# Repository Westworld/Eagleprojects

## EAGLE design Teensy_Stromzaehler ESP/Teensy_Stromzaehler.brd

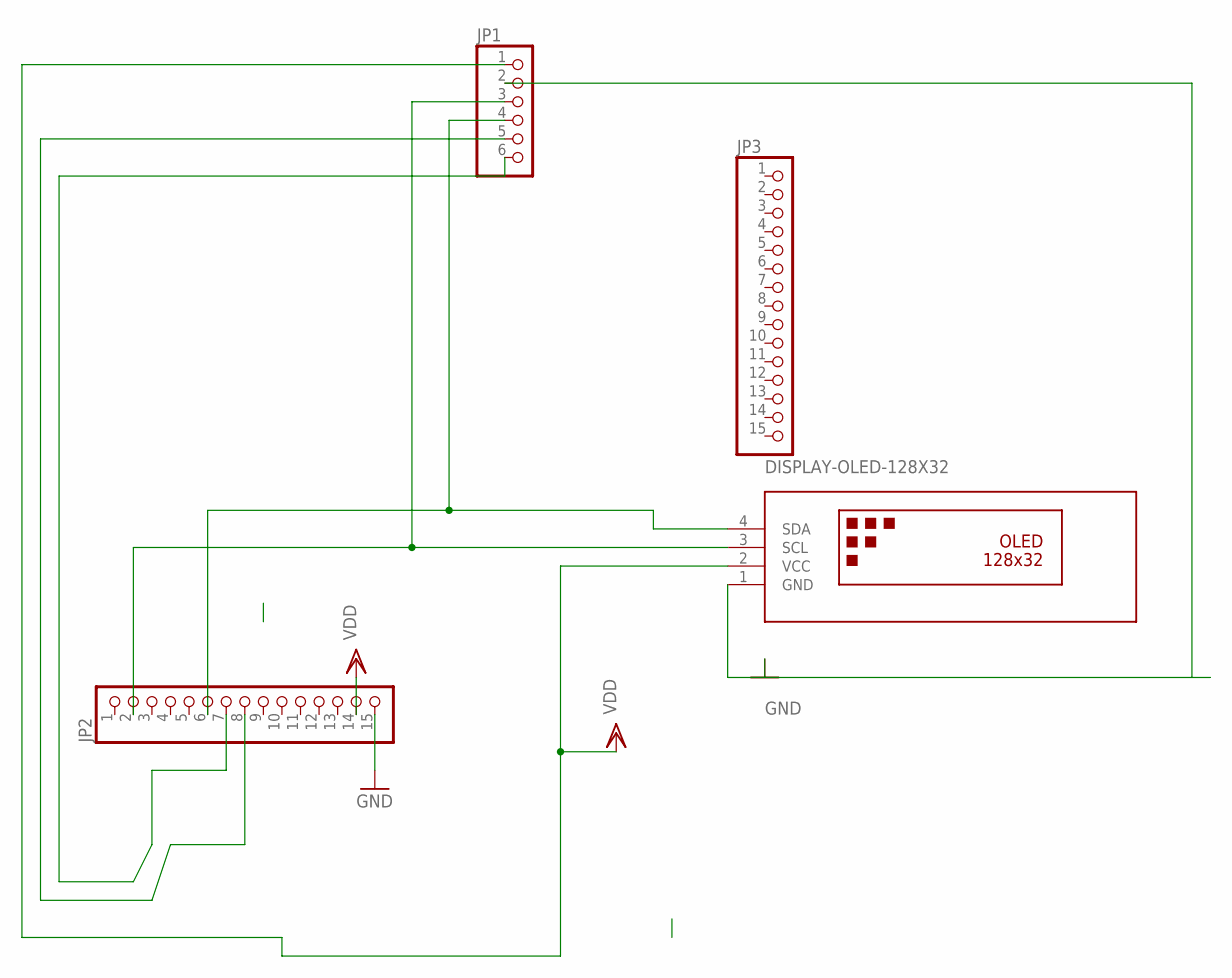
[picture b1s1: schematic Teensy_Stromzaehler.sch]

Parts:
JP1: PINHD-1X6; 1X06
JP2, JP3: PINHD-1X15; 1X15
U$3: DISPLAY-OLED-128X32

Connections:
GND: JP1.2, JP2.15, U$3.1 (GND)
unnamed: JP1.5, JP2.8
unnamed: JP1.6, JP2.7
unnamed: JP1.3, JP2.2, U$3.3 (SCL)
unnamed: JP1.4, JP2.6, U$3.4 (SDA)
VDD: JP1.1, JP2.14, U$3.2 (VCC)

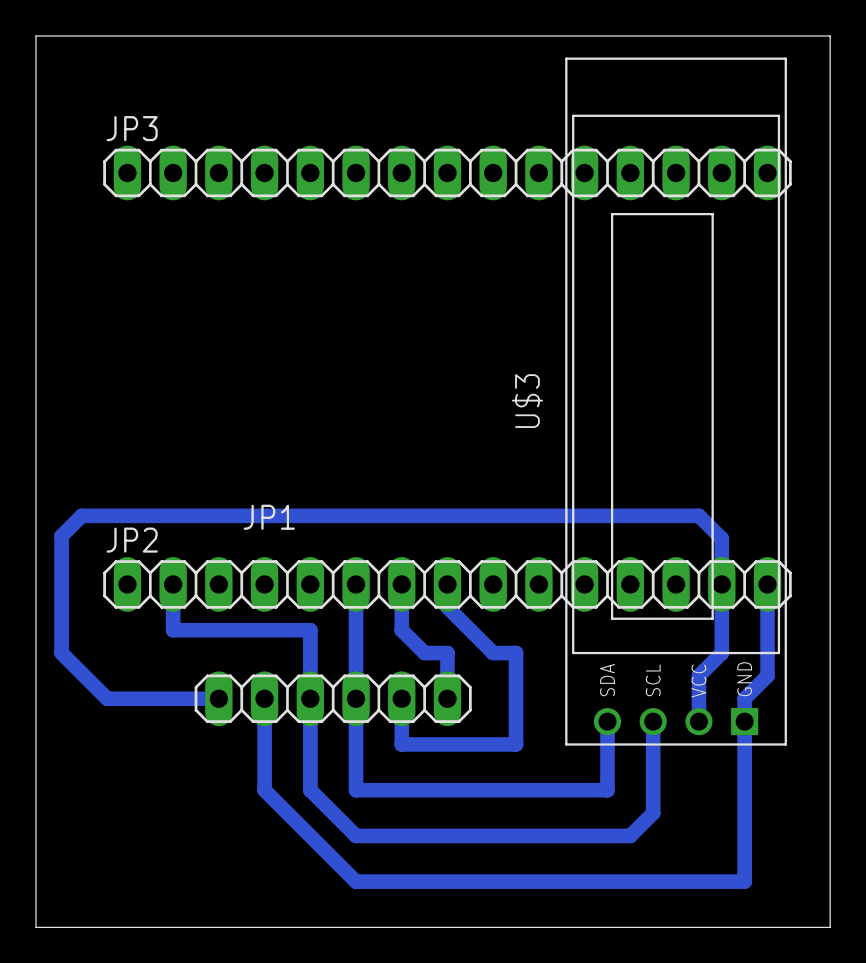
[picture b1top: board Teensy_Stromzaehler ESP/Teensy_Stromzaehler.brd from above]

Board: 2 copper layers, 44.1 x 49.5 mm, 4 parts (0 on the bottom side), 6 nets.

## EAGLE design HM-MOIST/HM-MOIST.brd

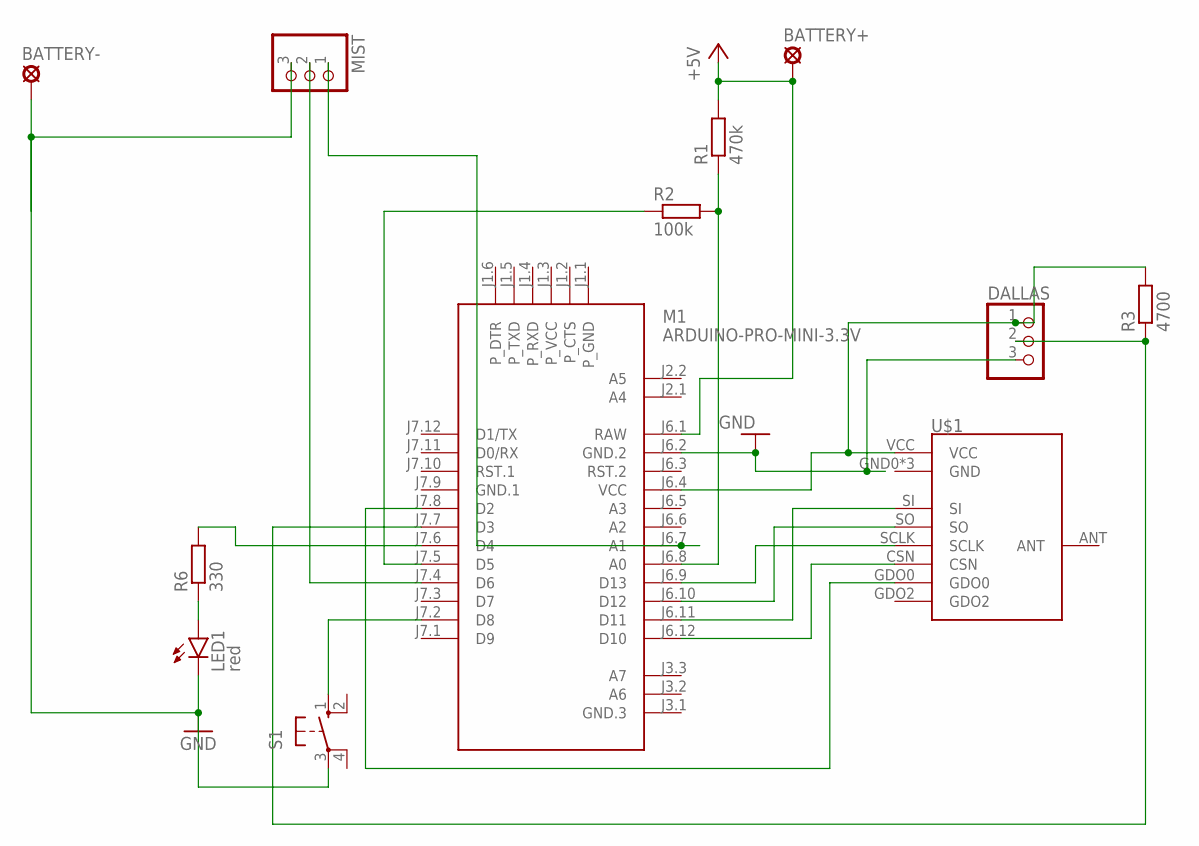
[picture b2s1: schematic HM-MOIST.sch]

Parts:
BATTERY+: LSP11
BATTERY-: LSP11
DALLAS: PINHD-1X3; 1X03
LED1: red; LED5MM
M1: ARDUINO-PRO-MINI-3.3V; ARDUINO-PRO-MINI
MIST: PINHD-1X3; 1X03
R1: 470k; M1206
R2: 100k; 0204/7
R3: 4700; 0204/7
R6: 330; M1206
S1: 10-XX; B3F-10XX
U$1: CC1101

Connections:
+5V: BATTERY+.MP, M1.J6.1 (RAW), R1.2
GND: BATTERY-.MP, DALLAS.3, LED1.K (C), M1.J6.2 (GND.2), MIST.3, S1.3, U$1.GND0 (GND), U$1.GND1 (GND), U$1.GND2 (GND)
GND.1: M1.J7.9 (GND.1)
unnamed: M1.J6.12 (D10), U$1.CSN
unnamed: M1.J7.8 (D2), U$1.GDO0
unnamed: M1.J6.11 (D11), U$1.SI
unnamed: M1.J6.10 (D12), U$1.SO
unnamed: M1.J6.9 (D13), U$1.SCLK
unnamed: LED1.A, R6.1
unnamed: M1.J7.2 (D8), S1.1 (S)
unnamed: M1.J7.6 (D4), R6.2
unnamed: M1.J6.8 (A0), R1.1, R2.2
unnamed: DALLAS.1, M1.J6.4 (VCC), R3.2, U$1.VCC
unnamed: M1.J7.5 (D5), R2.1
unnamed: M1.J7.4 (D6), MIST.2
unnamed: DALLAS.2, M1.J7.7 (D3), R3.1
unnamed: M1.J6.7 (A1), MIST.1

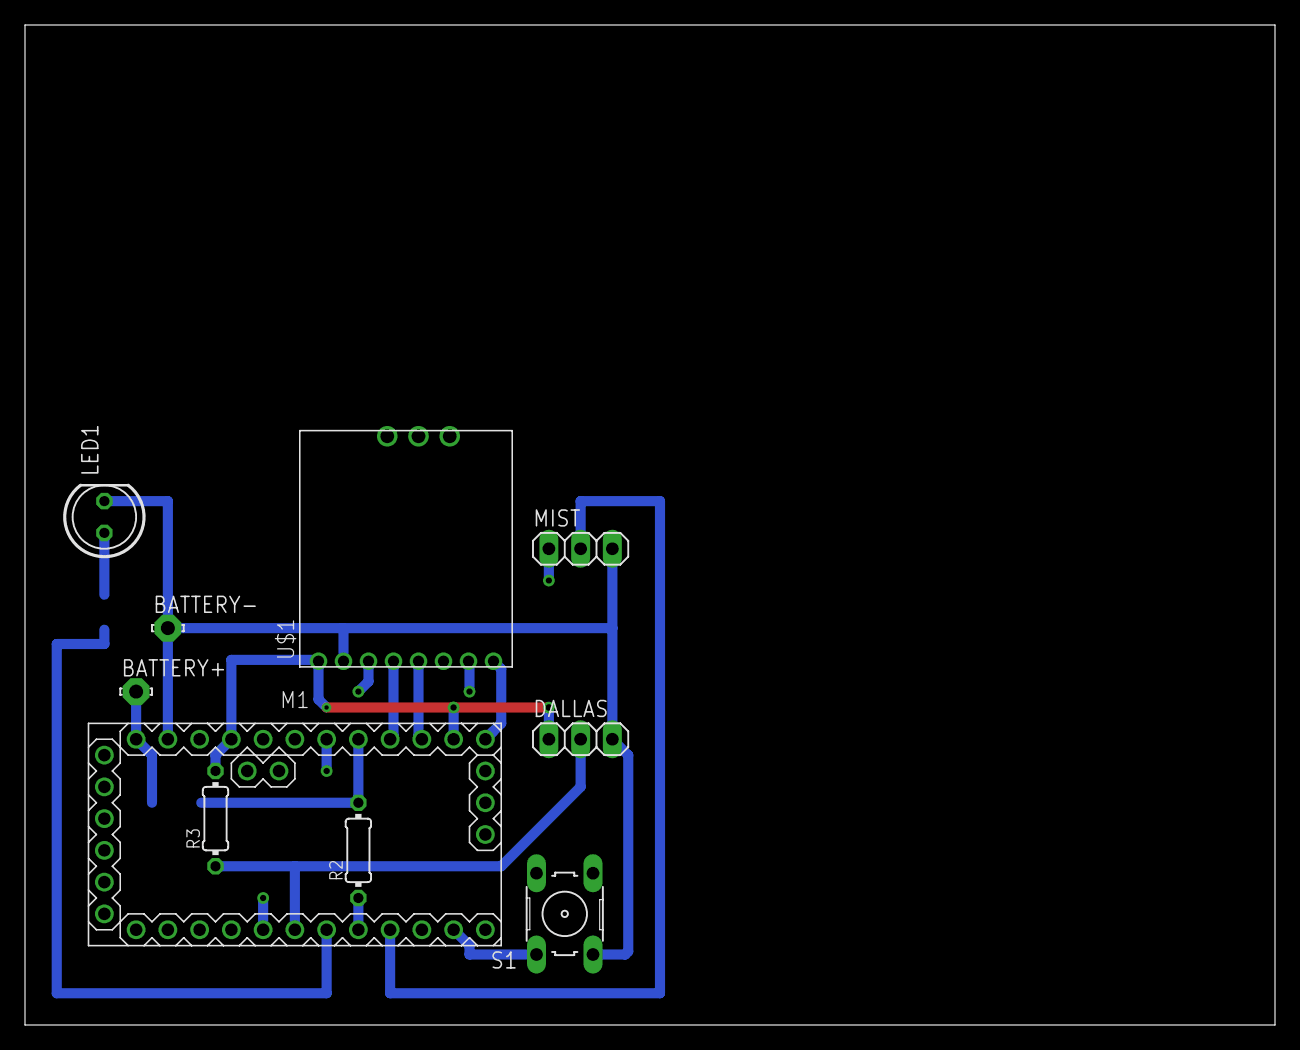
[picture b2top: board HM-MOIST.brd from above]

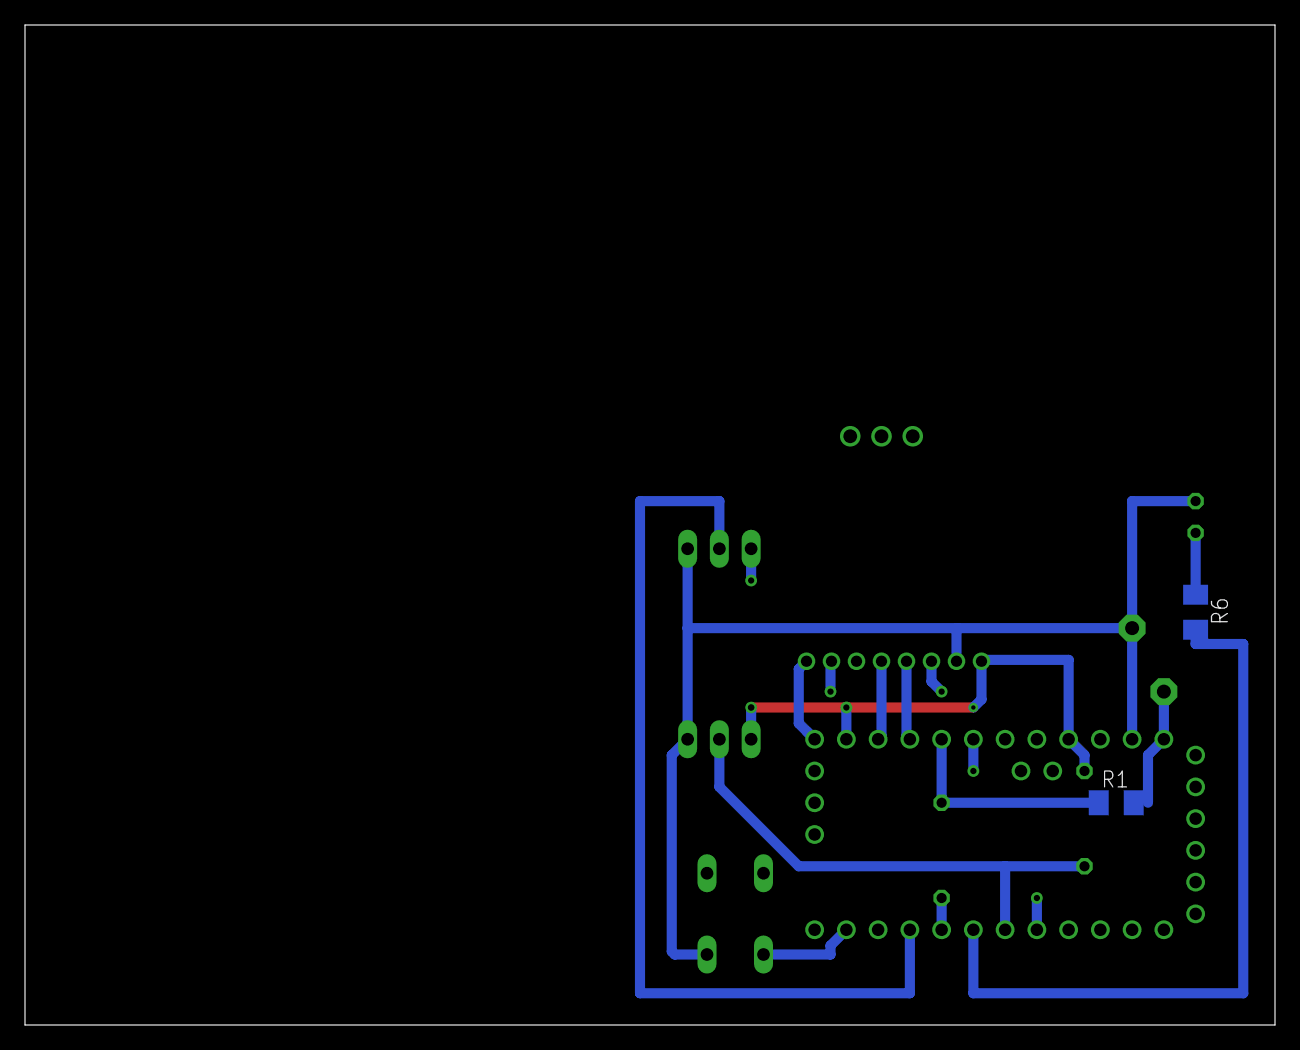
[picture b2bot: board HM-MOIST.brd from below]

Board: 2 copper layers, 100.0 x 80.0 mm, 12 parts (2 on the bottom side), 16 nets.

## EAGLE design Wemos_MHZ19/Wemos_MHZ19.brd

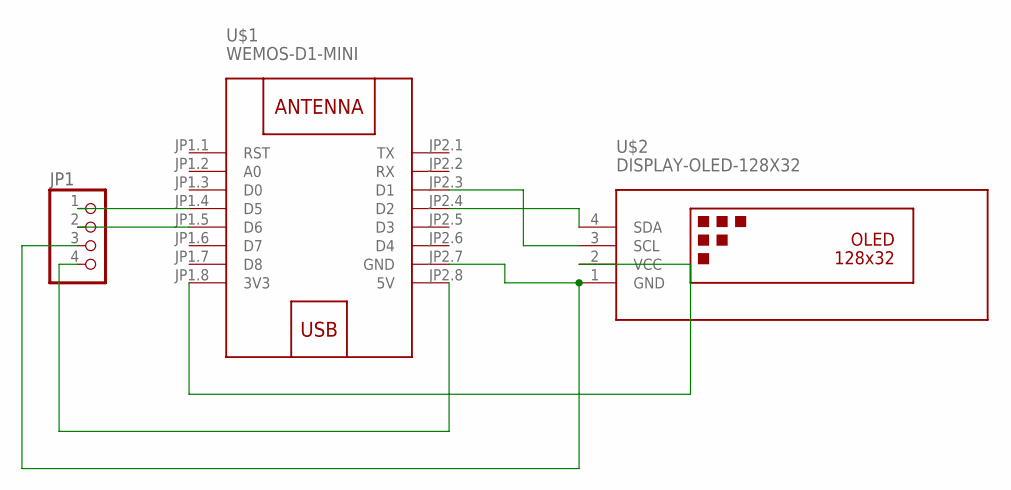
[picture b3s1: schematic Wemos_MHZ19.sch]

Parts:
JP1: PINHD-1X4/90; 1X04/90
U$1: WEMOS-D1-MINI
U$2: DISPLAY-OLED-128X32

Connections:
unnamed: JP1.3, U$1.JP2.7 (GND), U$2.1 (GND)
unnamed: U$1.JP1.8 (3V3), U$2.2 (VCC)
unnamed: U$1.JP2.4 (D2), U$2.4 (SDA)
unnamed: U$1.JP2.3 (D1), U$2.3 (SCL)
unnamed: JP1.4, U$1.JP2.8 (5V)
unnamed: JP1.2, U$1.JP1.5 (D6)
unnamed: JP1.1, U$1.JP1.4 (D5)

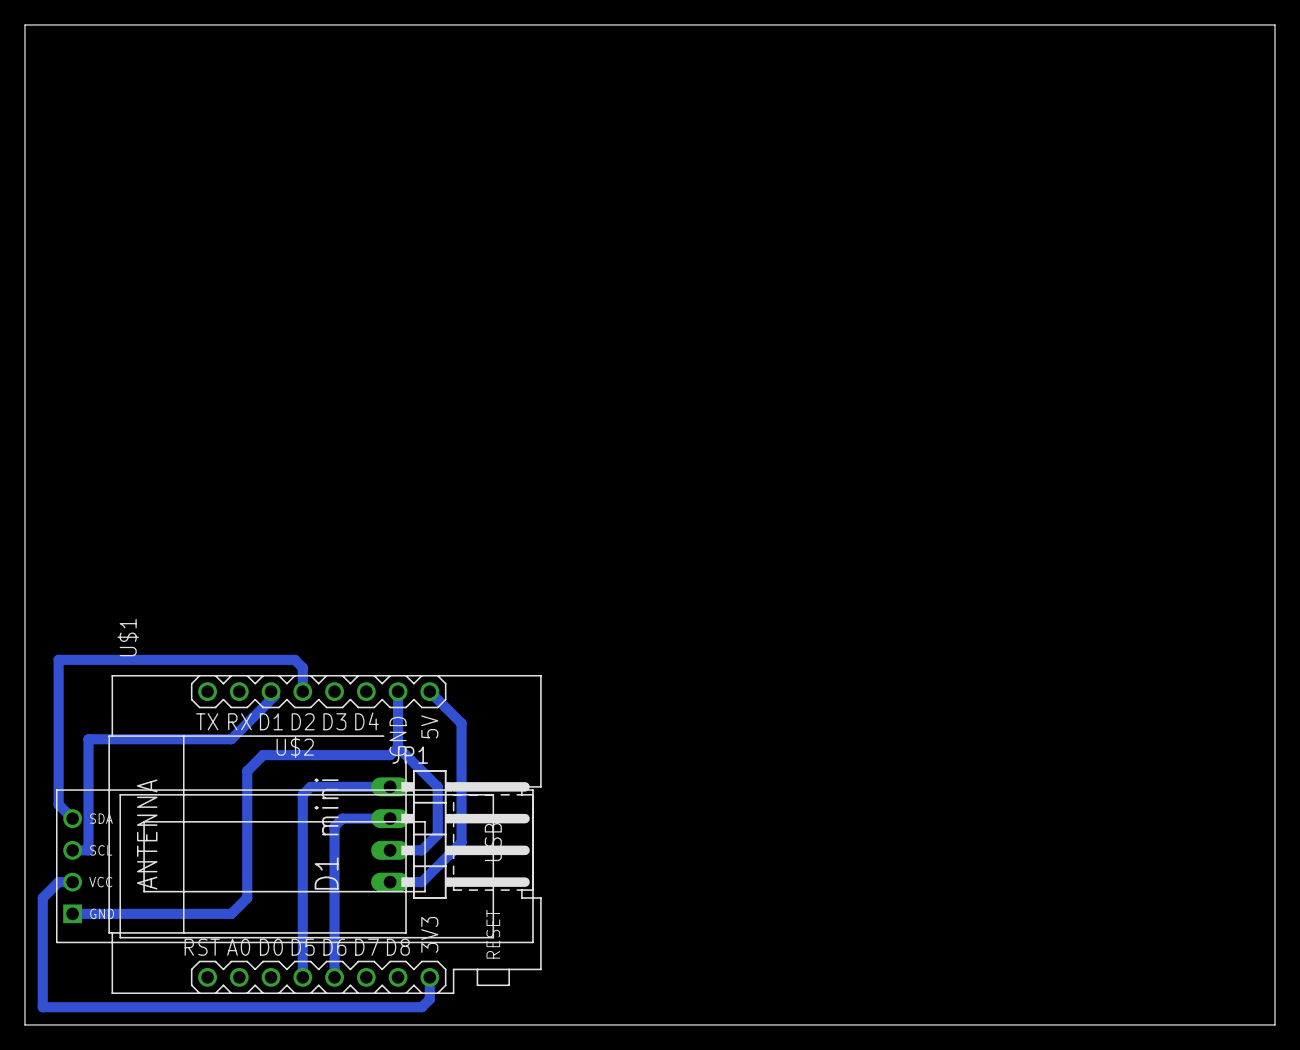
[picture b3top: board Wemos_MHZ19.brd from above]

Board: 2 copper layers, 100.0 x 80.0 mm, 3 parts (0 on the bottom side), 7 nets.

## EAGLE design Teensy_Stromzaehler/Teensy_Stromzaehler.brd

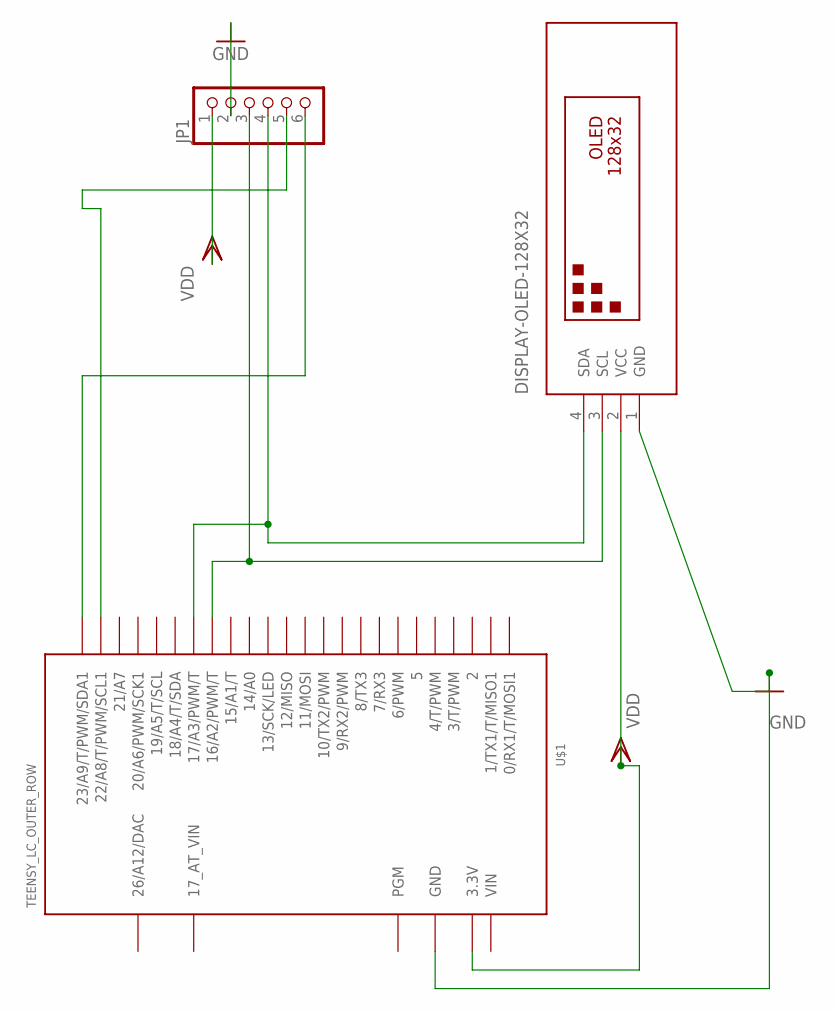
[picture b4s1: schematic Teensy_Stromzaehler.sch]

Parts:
JP1: PINHD-1X6; 1X06
U$1: TEENSY_LC_OUTER_ROW; TEENSY_3.0-3.2&LC_OUTER_ROW
U$3: DISPLAY-OLED-128X32

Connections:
26/A12/DAC: U$1.RESET/DAC (26/A12/DAC)
GND: JP1.2, U$1.AGND (GND), U$1.GND, U$1.GND1 (GND), U$3.1 (GND)
unnamed: JP1.5, U$1.22/A8 (22/A8/T/PWM/SCL1)
unnamed: JP1.6, U$1.23/A9 (23/A9/T/PWM/SDA1)
unnamed: JP1.3, U$1.16/A2 (16/A2/PWM/T), U$3.3 (SCL)
unnamed: JP1.4, U$1.17/A3 (17/A3/PWM/T), U$3.4 (SDA)
VDD: JP1.1, U$1.3.3V, U$1.3.3V1 (3.3V), U$3.2 (VCC)
VIN: U$1.VIN

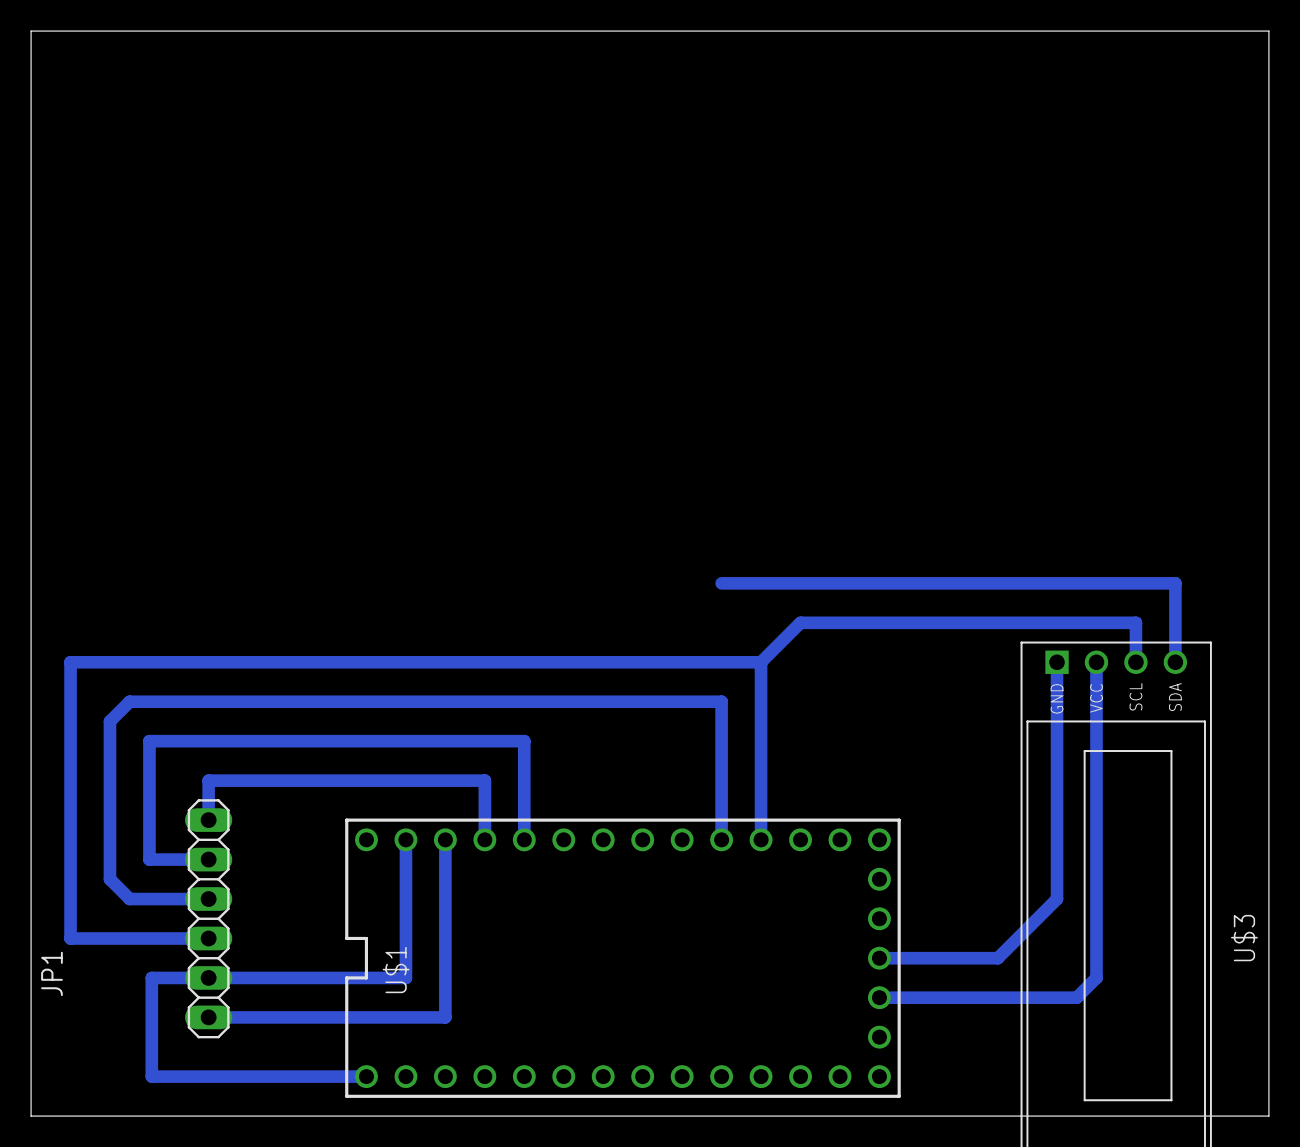
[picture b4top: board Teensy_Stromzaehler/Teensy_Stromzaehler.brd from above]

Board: 2 copper layers, 79.7 x 69.8 mm, 3 parts (0 on the bottom side), 6 nets.

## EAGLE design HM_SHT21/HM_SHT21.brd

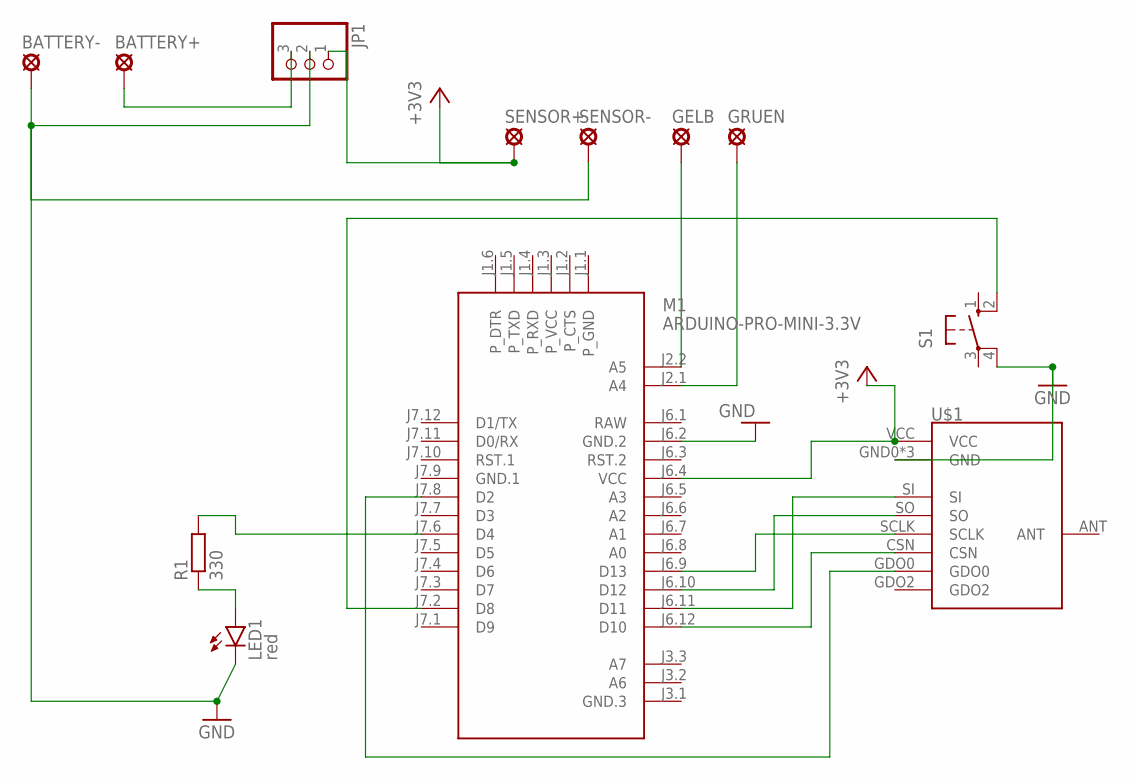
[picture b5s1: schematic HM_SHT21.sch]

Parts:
BATTERY+: LSP11
BATTERY-: LSP11
GELB: LSP11
GRUEN: LSP11
JP1: PINHD-1X3; 1X03
LED1: red; LED5MM
M1: ARDUINO-PRO-MINI-3.3V; ARDUINO-PRO-MINI
R1: 330; 0204/7
S1: 10-XX; B3F-10XX
SENSOR+: LSP11
SENSOR-: LSP11
U$1: CC1101

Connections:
+3V3: JP1.1, M1.J6.4 (VCC), SENSOR+.MP, U$1.VCC
GND: BATTERY-.MP, JP1.2, LED1.K (C), M1.J6.2 (GND.2), S1.4 (P1), SENSOR-.MP, U$1.GND0 (GND), U$1.GND1 (GND), U$1.GND2 (GND)
GND.1: M1.J7.9 (GND.1)
unnamed: M1.J6.12 (D10), U$1.CSN
unnamed: M1.J7.8 (D2), U$1.GDO0
unnamed: M1.J6.11 (D11), U$1.SI
unnamed: M1.J6.10 (D12), U$1.SO
unnamed: M1.J6.9 (D13), U$1.SCLK
unnamed: LED1.A, R1.1
unnamed: M1.J7.2 (D8), S1.2 (S1)
unnamed: M1.J7.6 (D4), R1.2
unnamed: GELB.MP, M1.J2.2 (A5)
unnamed: GRUEN.MP, M1.J2.1 (A4)
RAW: M1.J6.1 (RAW)
VIN: BATTERY+.MP, JP1.3

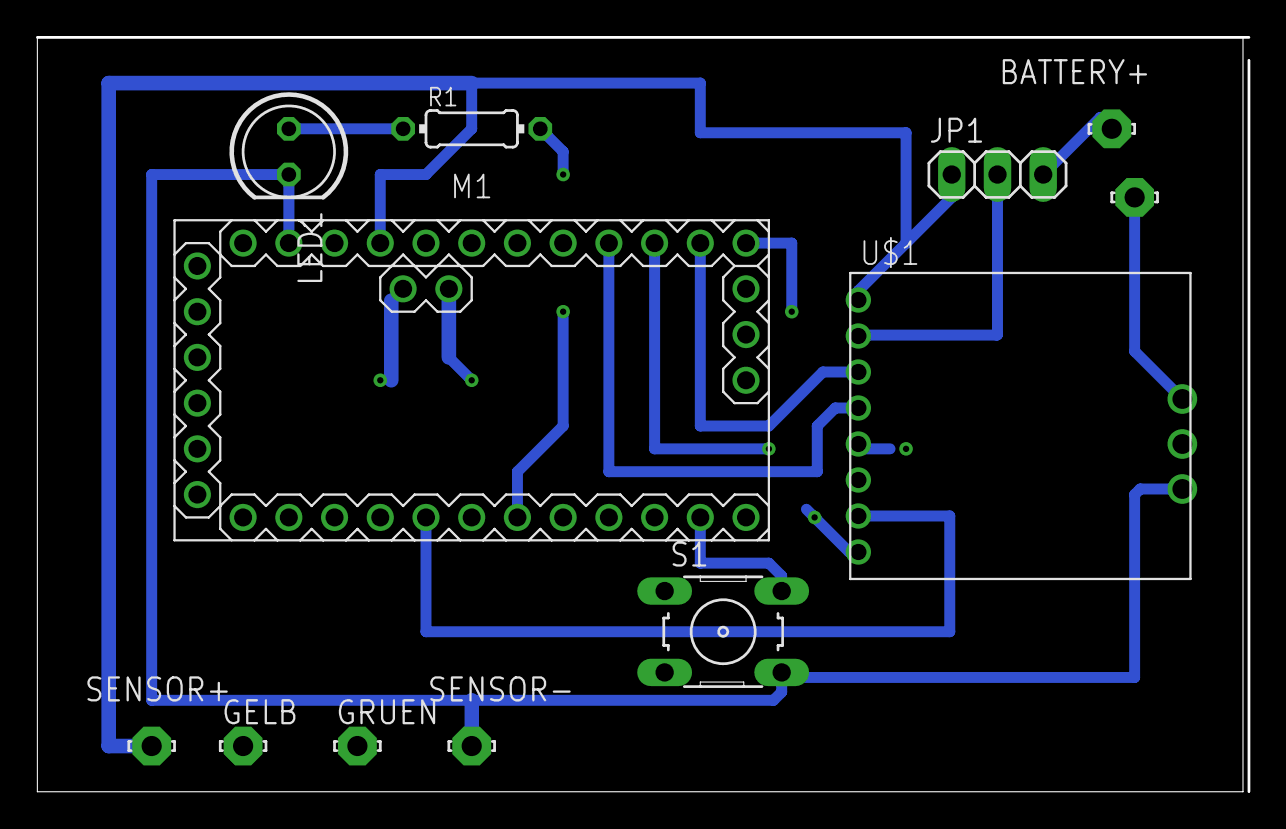
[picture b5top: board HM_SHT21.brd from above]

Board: 2 copper layers, 67.0 x 41.9 mm, 12 parts (0 on the bottom side), 13 nets.

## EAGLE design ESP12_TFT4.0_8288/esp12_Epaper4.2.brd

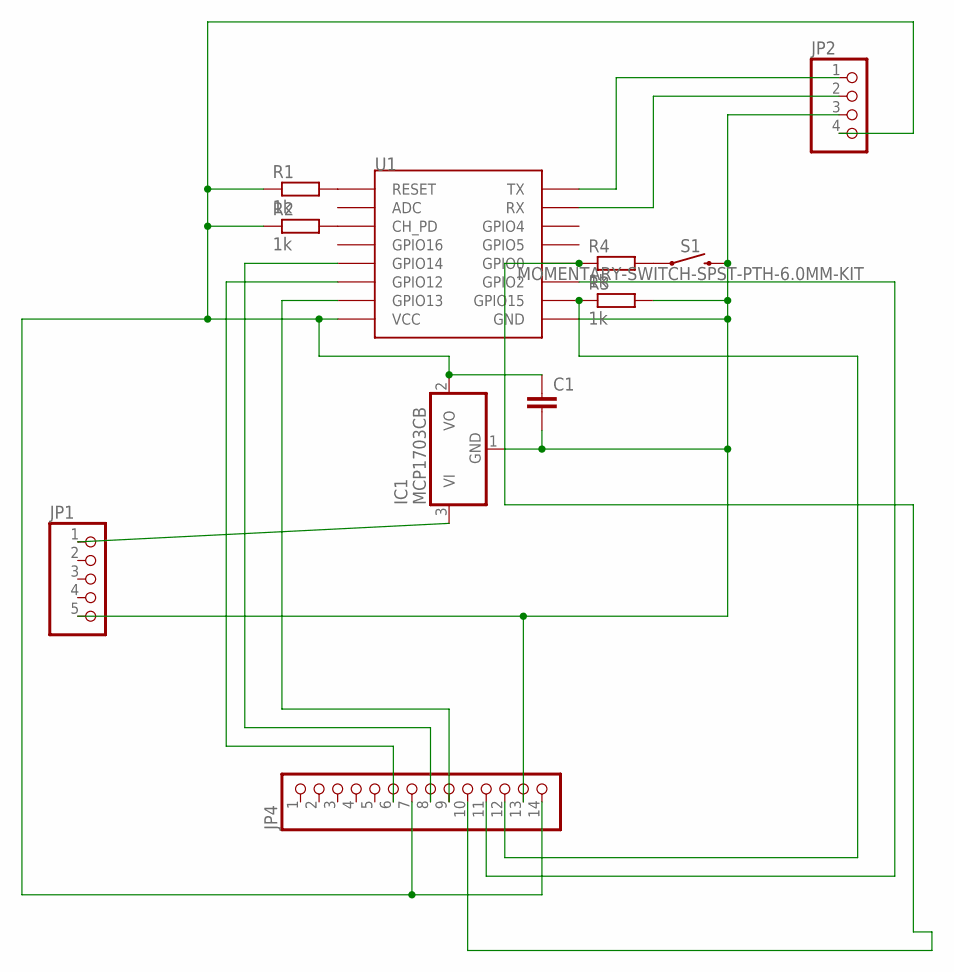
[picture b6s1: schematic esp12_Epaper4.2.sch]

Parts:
C1: C-EU025-050X050; C025-050X050
IC1: MCP1703CB; SOT23
JP1: PINHD-1X5; 1X05
JP2: PINHD-1X4/90; 1X04/90
JP4: PINHD-1X14; 1X14
R1, R2, R3, R4: 1k; R1206
S1: MOMENTARY-SWITCH-SPST-PTH-6.0MM-KIT; TACTILE_SWITCH_PTH_6.0MM_KIT
U1: ESP12

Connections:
GND: C1.2, IC1.1 (GND), JP1.5, JP2.3, JP4.13, R3.2, S1.3 (2), U1.GND
GPIO0CS: JP4.12, R3.1, U1.GPIO15
GPIO0_DC: JP4.10, R4.1, U1.GPIO0
GPIO2_RESET: JP4.11, U1.GPIO2
GPIO13_MOSI: JP4.9, U1.GPIO13
GPIO14_SCK: JP4.8, U1.GPIO14
unnamed: R1.2, U1.RESET
unnamed: R2.2, U1.CH_PD
unnamed: JP4.6, U1.GPIO12
unnamed: R4.2, S1.1
unnamed: JP2.1, U1.TX
unnamed: JP2.2, U1.RX
unnamed: IC1.3 (VI), JP1.1
VCC: C1.1, IC1.2 (VO), JP2.4, JP4.7, JP4.14, R1.1, R2.1, U1.VCC

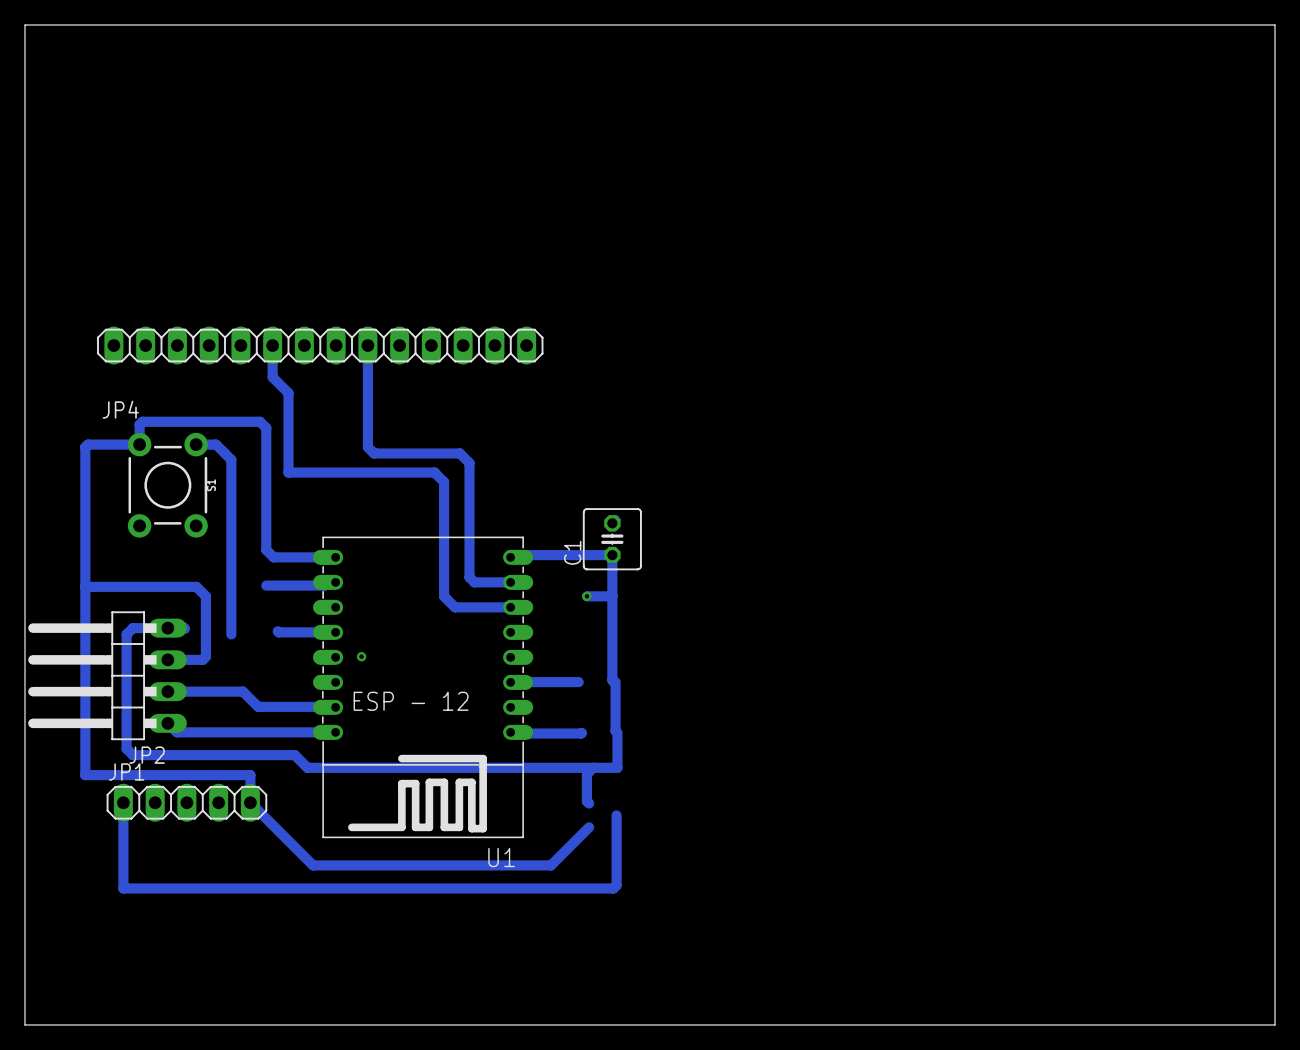
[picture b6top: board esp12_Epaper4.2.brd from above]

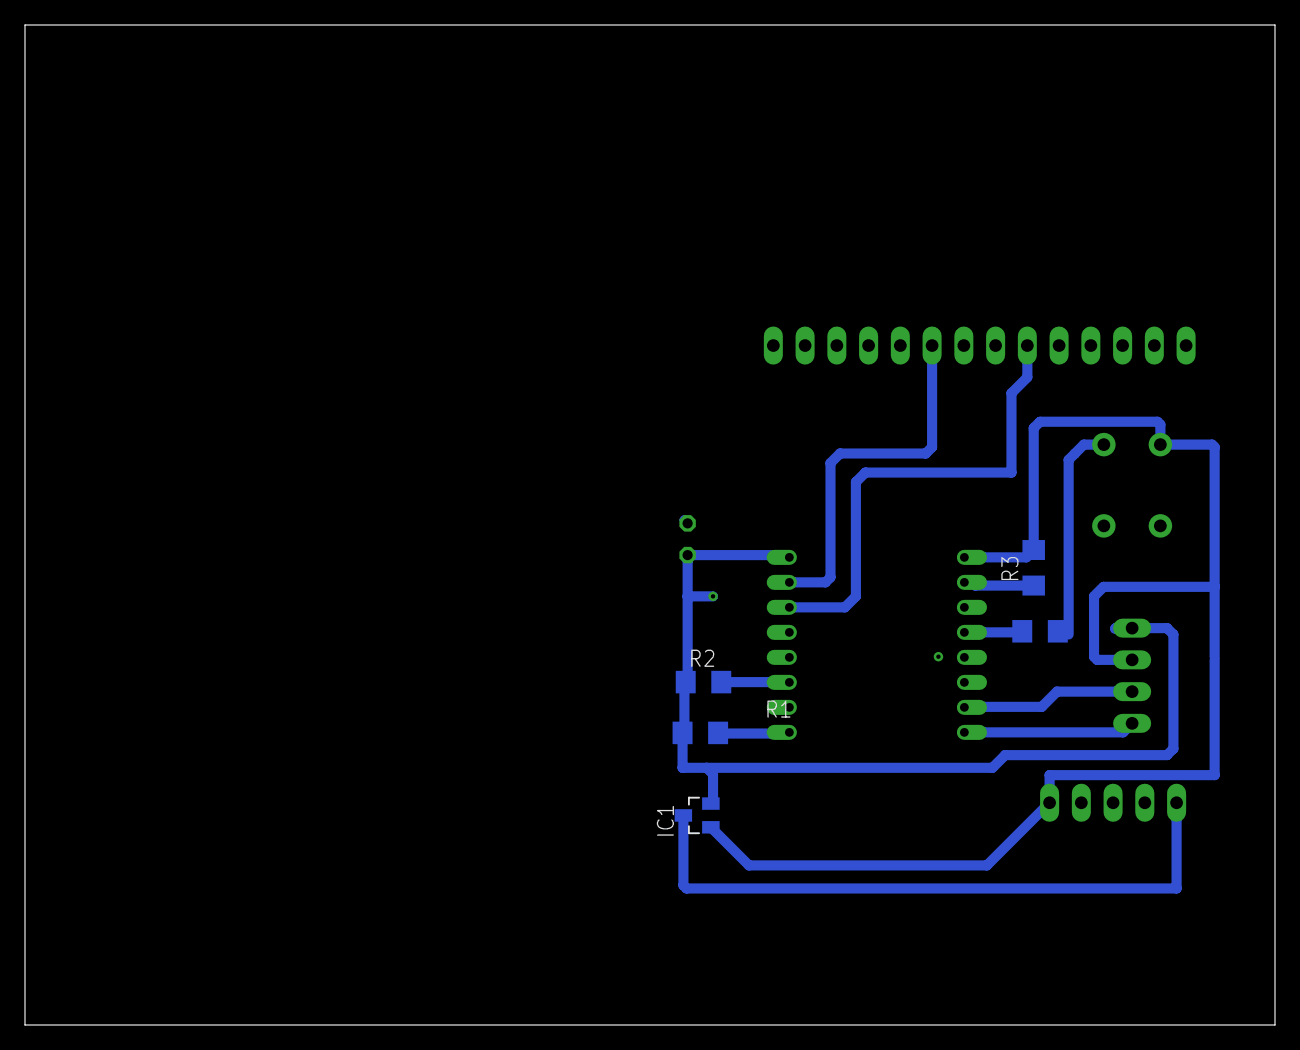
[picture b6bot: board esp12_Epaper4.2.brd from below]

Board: 2 copper layers, 100.0 x 80.0 mm, 11 parts (5 on the bottom side), 14 nets.

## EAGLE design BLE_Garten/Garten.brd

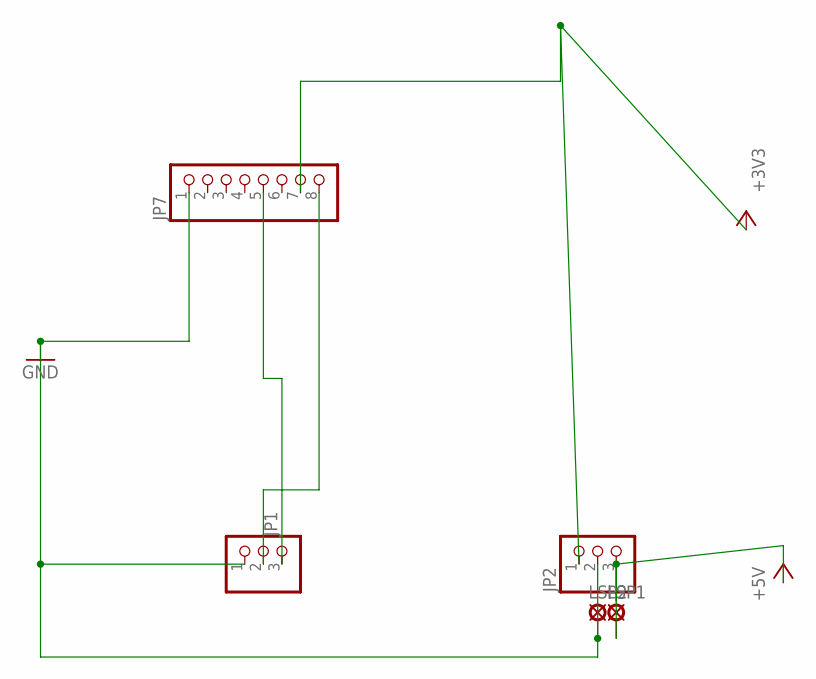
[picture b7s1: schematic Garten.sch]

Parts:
JP1, JP2: PINHD-1X3/90; 1X03/90
JP7: PINHD-1X8; 1X08
LSP1, LSP2: SE11

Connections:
+3V3: JP2.1, JP7.7
+5V: JP2.3, LSP1.MP
GND: JP1.1, JP2.2, JP7.1, LSP2.MP
SENSOR+: JP1.2, JP7.8
SENSOR_SIG: JP1.3, JP7.5

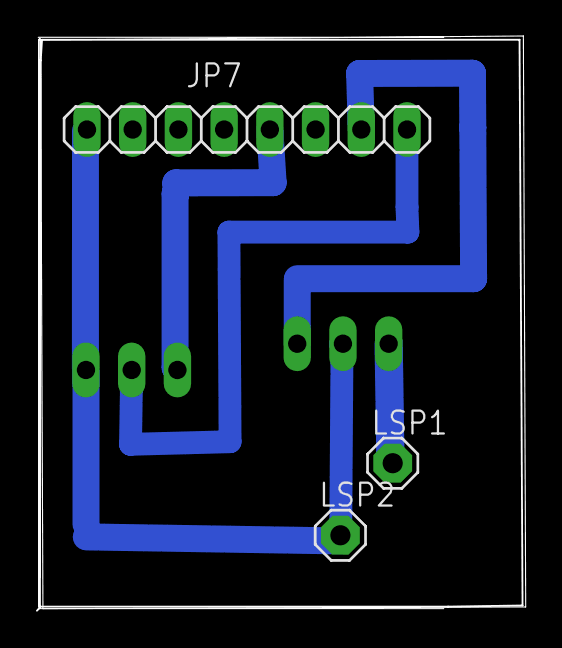
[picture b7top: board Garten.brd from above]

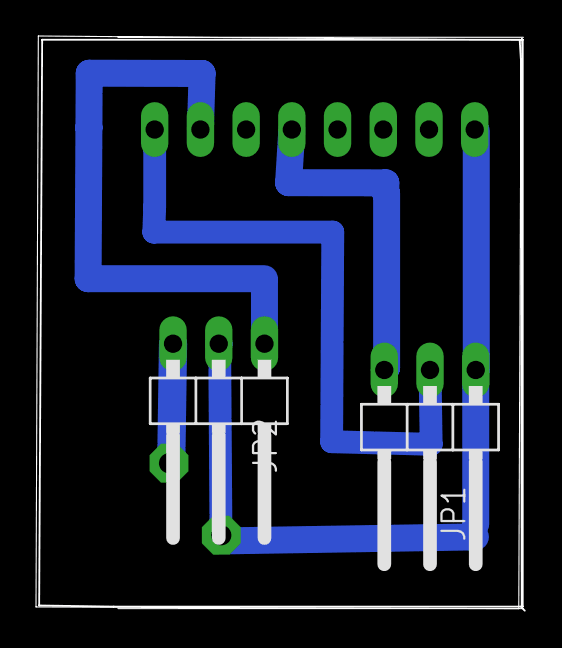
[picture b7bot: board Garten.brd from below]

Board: 2 copper layers, 27.0 x 31.8 mm, 5 parts (2 on the bottom side), 5 nets.

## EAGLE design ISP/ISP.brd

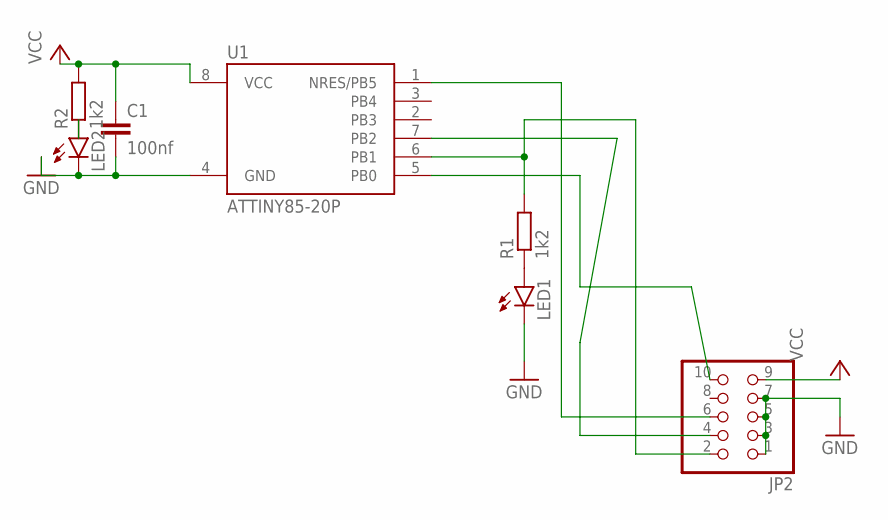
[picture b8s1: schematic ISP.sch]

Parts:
C1: 100nf; C5B2.5
JP2: PINHD-2X5; 2X05
LED1, LED2: LED5MM
R1, R2: 1k2; 0204/7
U1: ATTINY85-20P; PDIP08_300MIL

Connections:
GND: C1.2, JP2.1, JP2.3, JP2.5, JP2.7, LED1.K (C), LED2.K (C), U1.4 (GND)
unnamed: JP2.6, U1.1 (NRES/PB5)
unnamed: JP2.4, U1.7 (PB2)
unnamed: JP2.2, R1.2, U1.6 (PB1)
unnamed: JP2.10, U1.5 (PB0)
unnamed: LED1.A, R1.1
unnamed: LED2.A, R2.1
VCC: C1.1, JP2.9, R2.2, U1.8 (VCC)

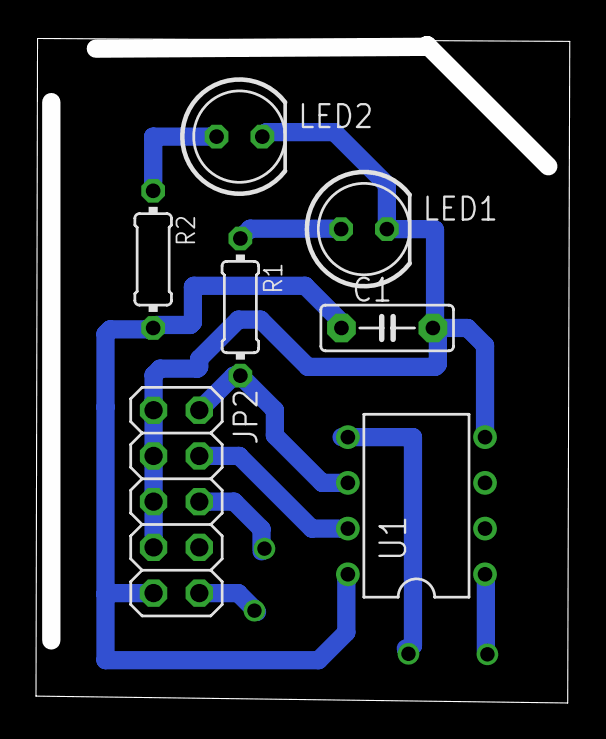
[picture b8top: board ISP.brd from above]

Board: 2 copper layers, 29.7 x 36.9 mm, 7 parts (0 on the bottom side), 8 nets.

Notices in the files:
parts and their libraries:
SparkFun-Switches: Licensing: Creative Commons ShareAlike 4.0 International - https://creativecommons.org/licenses/by-sa/4.0
diy-modules: Released under the Creative Commons Attribution 4.0 International License: http://creativecommons.org/licenses/by/4.0
